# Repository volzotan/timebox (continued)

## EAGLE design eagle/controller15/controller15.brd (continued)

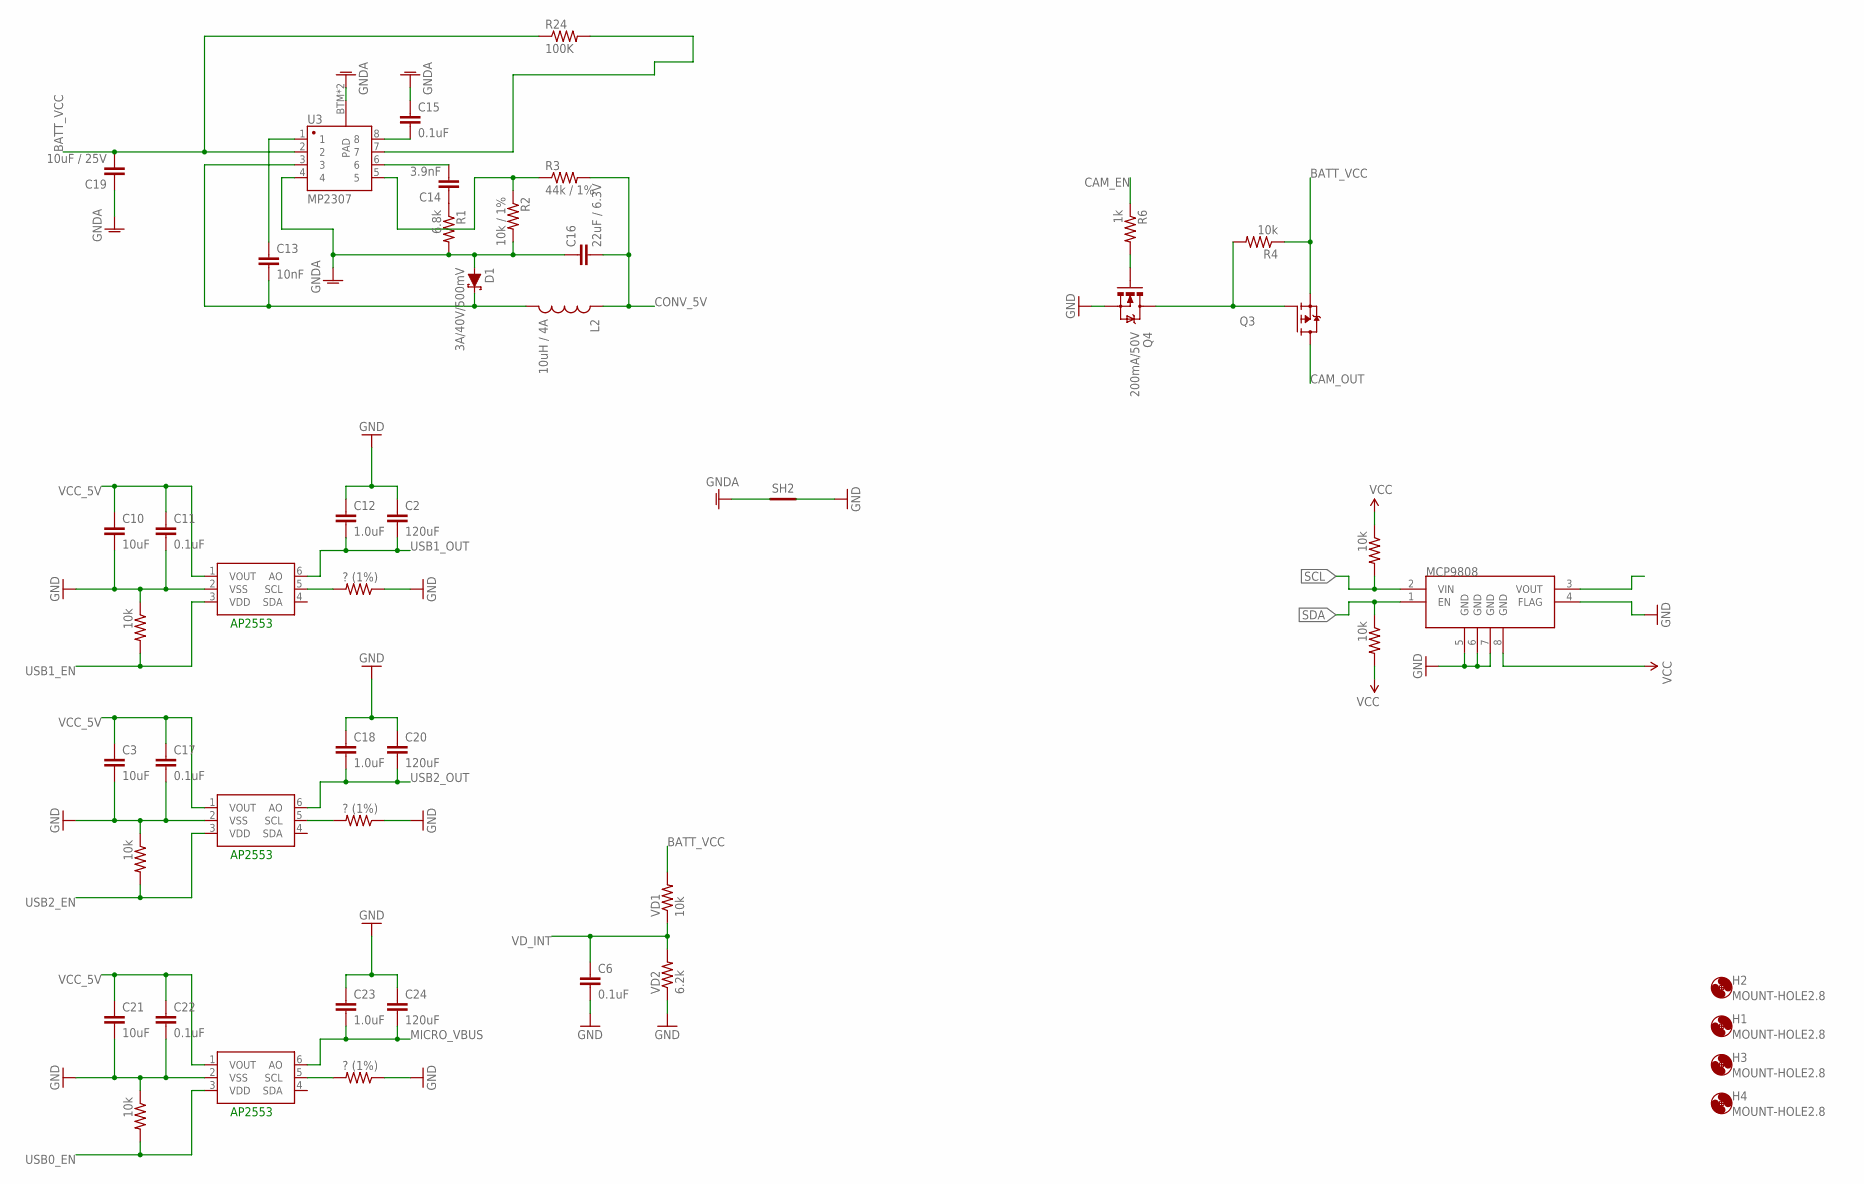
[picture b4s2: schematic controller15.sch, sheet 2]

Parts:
AP1, AP2, AP2553: MCP4725; SOT23-6
C2, C20, C24: 120uF; 1206
C3, C10, C21: 10uF; 1206
C6, C15: 0.1uF; 1206
C11, C17, C22: 0.1uF; 0805
C12, C18, C23: 1.0uF; 1206
C13: 10nF; 0805
C14: 3.9nF; 1206
C16: 22uF / 6.3V; 1210
C19: 10uF / 25V; 1210
D1: 3A/40V/500mV; SMA-DIODE
H1, H2, H3, H4: MOUNT-HOLE2.8; 2,8
L2: 10uH / 4A; SRU1038
MCP9808: V_REG_MIC5216; MSOP8
Q3: FDD4141TO252; TO252
Q4: 200mA/50V; SOT23-3
R1: 6.8k; 1206
R2: 10k / 1%; 1206
R3: 44k / 1%; 1206
R4: 10k; 0805
R6: 1k; 0805
R24: 100K; 1206
R_I2C_1, R_I2C_2: 10k; 0805
R_MOSFET_USB1, R_MOSFET_USB2, R_MOSFET_USB5: ? (1%); 0805
R_MOSFET_USB3, R_MOSFET_USB4, R_MOSFET_USB6: 10k; 0805
SH2: SHORT-HT5; SHORT_TOP-50
U3: MP2307; SO08
VD1: 10k; 1206
VD2: 6.2k; 1206

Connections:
BATT_VCC: C19.2, Q3.2 (S), R4.1, R24.1, U3.2, VD1.2; also elsewhere on the board
CAM_EN: R6.1; also elsewhere on the board
CAM_OUT: Q3.3 (D); also elsewhere on the board
CONV_5V: C16.2, L2.1, R3.2
GND: AP1.2 (VSS), AP2.2 (VSS), AP2553.2 (VSS), C2.1, C3.2, C6.2, C10.2, C11.2, C12.1, C17.2, C18.1, C20.1, C21.2, C22.2, C23.1, C24.1, MCP9808.4 (FLAG), MCP9808.5 (GND), MCP9808.6 (GND), MCP9808.7 (GND), Q4.2 (S), R_MOSFET_USB1.1, R_MOSFET_USB2.1, R_MOSFET_USB3.1, R_MOSFET_USB4.1, R_MOSFET_USB5.1, R_MOSFET_USB6.1, SH2.2, VD2.1; also elsewhere on the board
GNDA: C15.1, C16.1, C19.1, D1.A, R1.2, R2.2, SH2.1, U3.4, U3.BTM (PAD), U3.P$1 (PAD)
MICRO_VBUS: AP2.6 (AO), C23.2, C24.2; also elsewhere on the board
unnamed: Q4.1 (G), R6.2
unnamed: Q3.1 (G), Q4.3 (D), R4.2
unnamed: AP2553.5 (SCL), R_MOSFET_USB1.2
unnamed: AP1.5 (SCL), R_MOSFET_USB2.2
unnamed: AP2.5 (SCL), R_MOSFET_USB5.2
unnamed: C15.2, U3.8
unnamed: C13.2, D1.C, L2.2, U3.3
unnamed: C13.1, U3.1
unnamed: C14.1, R1.1
unnamed: C14.2, U3.6
unnamed: R2.1, R3.1, U3.5
PB_BUCK_EN: R24.2, U3.7
SCL: MCP9808.2 (VIN), R_I2C_1.2; also elsewhere on the board
SDA: MCP9808.1 (EN), R_I2C_2.1; also elsewhere on the board
USB0_EN: AP2.3 (VDD), R_MOSFET_USB6.2; also elsewhere on the board
USB1_EN: AP2553.3 (VDD), R_MOSFET_USB3.2; also elsewhere on the board
USB1_OUT: AP2553.6 (AO), C2.2, C12.2; also elsewhere on the board
USB2_EN: AP1.3 (VDD), R_MOSFET_USB4.2; also elsewhere on the board
USB2_OUT: AP1.6 (AO), C18.2, C20.2; also elsewhere on the board
VCC: MCP9808.8 (GND), R_I2C_1.1, R_I2C_2.2; also elsewhere on the board
VCC_5V: AP1.1 (VOUT), AP2.1 (VOUT), AP2553.1 (VOUT), C3.1, C10.1, C11.1, C17.1, C21.1, C22.1; also elsewhere on the board
VD_INT: C6.1, VD1.1, VD2.2; also elsewhere on the board

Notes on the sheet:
AP2553

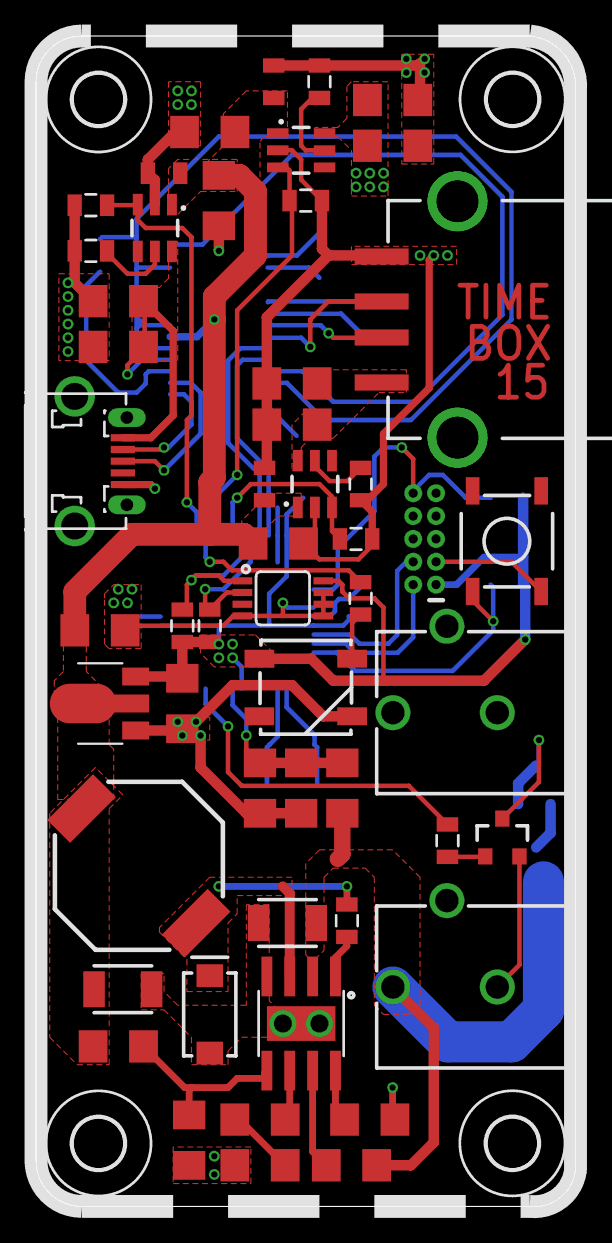
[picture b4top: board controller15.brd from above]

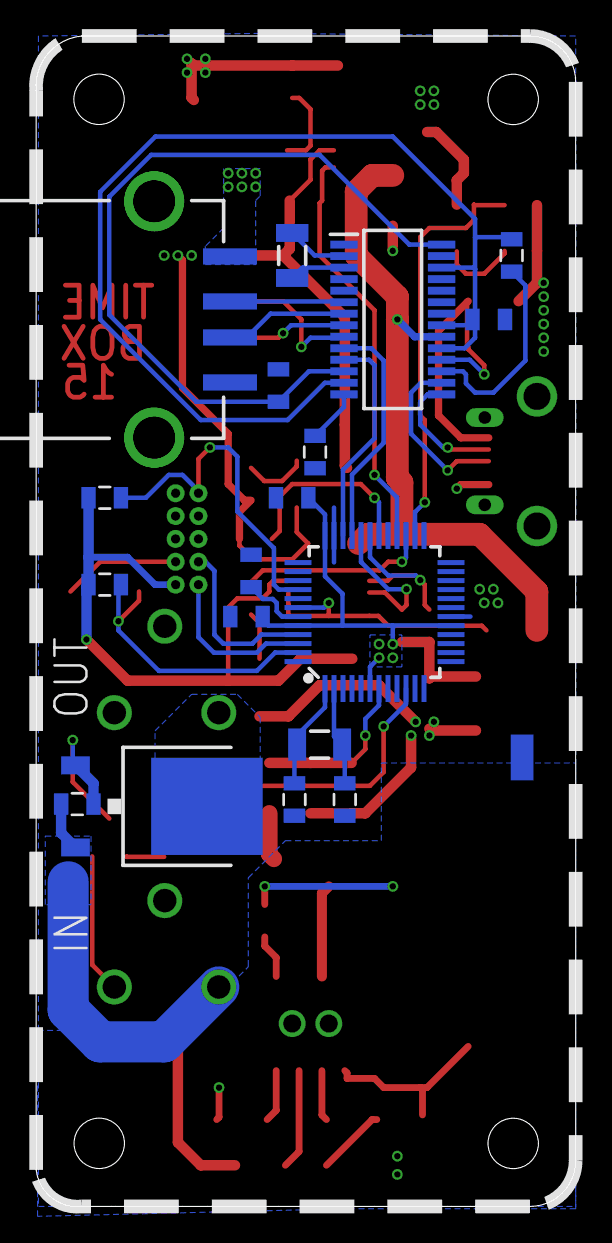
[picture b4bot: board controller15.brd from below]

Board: 2 copper layers, 30.0 x 65.0 mm, 75 parts (19 on the bottom side), 52 nets.
